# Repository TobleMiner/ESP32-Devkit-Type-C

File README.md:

ESP32 Devkit Type C
===================

This PCB is a USB Type C enabled ESP32 development board. It is pin-compatible
with the ESP32 Devkit C but sports a slightly decreased width to fit on a
standard breadboard.  
The current revision (Rev E) has been tested and confirmed to work fine.

# Features

* USB Type C
* pin-compatible with ESP32 Devkit
* fits on standard breadboard
* onboard antenna
* jumper to short USB protection diode

Furthermore this board is optimized for JLCPCB assembly, a Chinese SMT PCB
assembly service. All components on this board, except the USB Type C connector,
the push buttons and the pin headers can be assembled by them for around ~$8
including PCB manufacturing and components.

# Assembly

There is an
[interactive HTML BOM](https://tobleminer.github.io/ESP32-Devkit-Type-C/ibom.html)
to help you assemble the board.

Assuming you are using JLCPCB SMT assembly you will need to populate just the
following parts by hand:

| Reference  | Description            | LCSC                                                                                                                  |
|------------|------------------------|-----------------------------------------------------------------------------------------------------------------------|
| J1         | USB Type C connector   | [C167321](https://lcsc.com/product-detail/USB-Connectors_Jing-Extension-of-the-Electronic-Co-C167321_C167321.html)    |
| SW1, SW2   | RESET/BOOT push button | [C115357](https://lcsc.com/product-detail/Tactile-Switches_ALPS_SKRKAEE020_3-4-2-1-57N_C115357.html)    |
| J2, J3     | Pin headers            | [C2337](https://lcsc.com/product-detail/Pin-Header-Female-Header_BOOMELE-Boom-Precision-Elec-2-54mm-1x40P_C2337.html) |

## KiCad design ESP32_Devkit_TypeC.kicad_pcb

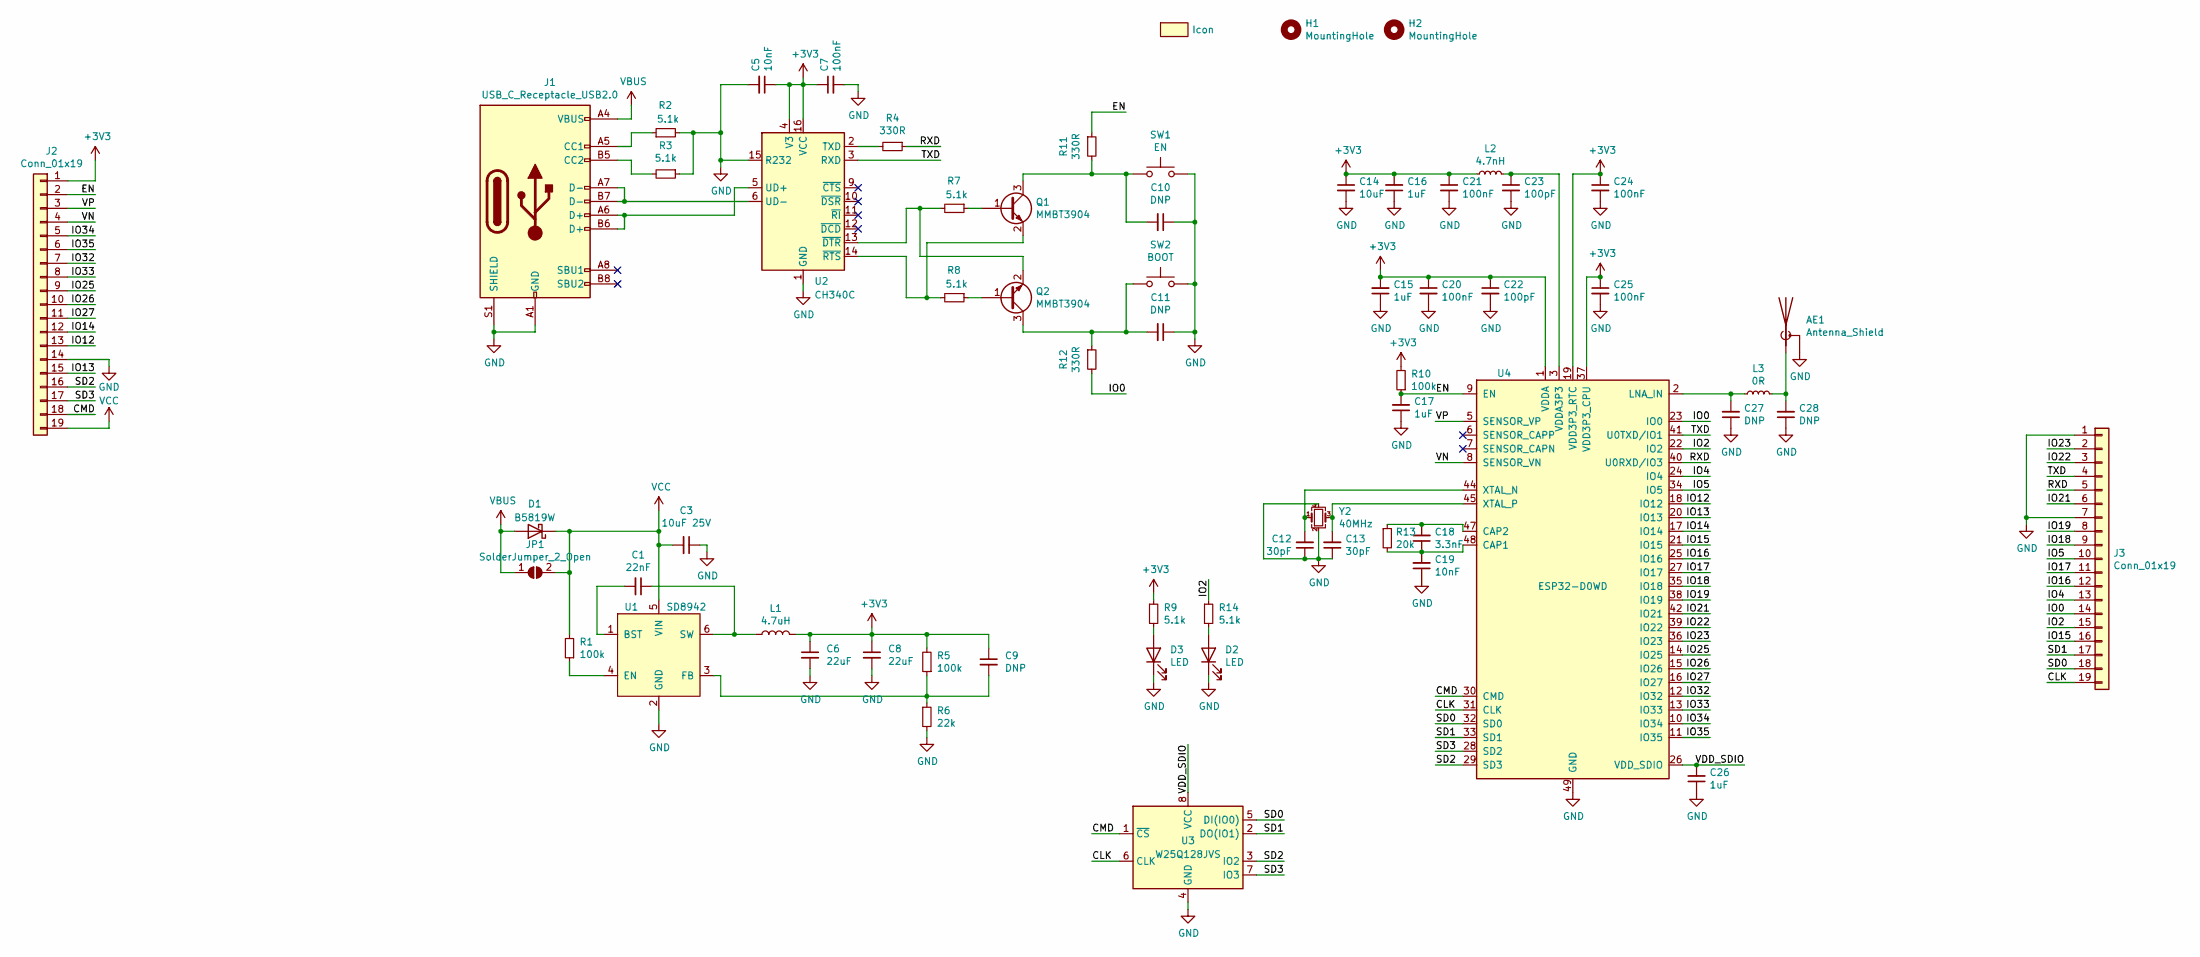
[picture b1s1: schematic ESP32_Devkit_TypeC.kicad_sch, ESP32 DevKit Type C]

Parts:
AE1: Antenna_Shield; Antenna_IFA_2.4GHz_meandered_mirrored
C1: 22nF; C_0402_1005Metric; LCSC C1532
C3: 10uF 25V; C_0805_2012Metric; LCSC C15850
C5, C19: 10nF; C_0402_1005Metric; LCSC C15195
C6, C8: 22uF; C_0603_1608Metric; LCSC C59461
C7, C20, C21, C24, C25: 100nF; C_0402_1005Metric; LCSC C1525
C9, C10, C11, C28: DNP; C_0402_1005Metric
C12, C13: 30pF; C_0402_1005Metric; LCSC C1570
C14: 10uF; C_0402_1005Metric; LCSC C15525
C15, C16, C17, C26: 1uF; C_0402_1005Metric; LCSC C52923
C18: 3.3nF; C_0402_1005Metric; LCSC C26404
C22, C23: 100pF; C_0402_1005Metric; LCSC C1546
C27: DNP; L3
D1: B5819W; D_SOD-123; LCSC C8598
D2, D3: LED; LED_0603_1608Metric_Castellated; LCSC C2286
H1, H2: MountingHole; ToolingHole_JLCSMT
I2: Icon; OSHW_icon_3.3x3
J1: USB_C_Receptacle_USB2.0; USB_C_Receptacle_Palconn_UTC16-G; LCSC C167321
J2, J3: Conn_01x19; PinHeader_1x19_P2.54mm_Vertical; LCSC C2894942
JP1: SolderJumper_2_Open; SolderJumper-2_P1.3mm_Open_Pad1.0x1.5mm
L1: 4.7uH; L_1210_3225Metric; LCSC C90319
L2: 4.7nH; L_0603_1608Metric; LCSC C13818
L3: 0R; L_0402_1005Metric; LCSC C17168
Q1, Q2: MMBT3904; SOT-23; LCSC C20526
R1, R5, R10: 100k; R_0402_1005Metric; LCSC C25741
R2, R3, R7, R8, R9, R14: 5.1k; R_0402_1005Metric; LCSC C25905
R4, R11, R12: 330R; R_0402_1005Metric; LCSC C25104
R6: 22k; R_0402_1005Metric; LCSC C25768
R13: 20k; R_0402_1005Metric; LCSC C25765
SW1: EN; SW_Push_SPST_NO_Alps_SKRK; LCSC C202388
SW2: BOOT; SW_Push_SPST_NO_Alps_SKRK; LCSC C202388
U1: SD8942; SOT-23-6; LCSC C250795
U2: CH340C; SOIC-16_3.9x9.9mm_P1.27mm; LCSCL C84681
U3: W25Q128JVS; SOIC-8_5.23x5.23mm_P1.27mm; LCSC C97521
U4: ESP32-D0WD; QFN-48-1EP_5x5mm_P0.35mm_EP3.7x3.7mm_ThermalVias; LCSC C967020
Y2: 40MHz; Crystal_SMD_2520-4Pin_2.5x2.0mm; LCSC C426970

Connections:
+3V3: C5.1, C6.1, C7.1, C8.1, C9.1, C14.1, C15.2, C16.2, C20.1, C21.1, C22.1, C24.1, C25.1, J2.1, L1.2, L2.1, R5.2, R9.1, R10.2, U2.4 (V3), U2.16 (VCC), U4.1 (VDDA), U4.19 (VDD3P3_RTC), U4.37 (VDD3P3_CPU), U4.43 (VDDA), U4.46 (VDDA)
/CLK: J3.19, U3.6 (CLK), U4.31 (CLK)
/CMD: J2.18, U3.1 (~CS), U4.30 (CMD)
/EN: C17.2, J2.2, R10.1, R11.1, U4.9 (EN)
/IO0: J3.14, R12.2, U4.23 (IO0)
/IO2: J3.15, R14.1, U4.22 (IO2)
/IO4: J3.13, U4.24 (IO4)
/IO5: J3.10, U4.34 (IO5)
/IO12: J2.13, U4.18 (IO12)
/IO13: J2.15, U4.20 (IO13)
/IO14: J2.12, U4.17 (IO14)
/IO15: J3.16, U4.21 (IO15)
/IO16: J3.12, U4.25 (IO16)
/IO17: J3.11, U4.27 (IO17)
/IO18: J3.9, U4.35 (IO18)
/IO19: J3.8, U4.38 (IO19)
/IO21: J3.6, U4.42 (IO21)
/IO22: J3.3, U4.39 (IO22)
/IO23: J3.2, U4.36 (IO23)
/IO25: J2.9, U4.14 (IO25)
/IO26: J2.10, U4.15 (IO26)
/IO27: J2.11, U4.16 (IO27)
/IO32: J2.7, U4.12 (IO32)
/IO33: J2.8, U4.13 (IO33)
/IO34: J2.5, U4.10 (IO34)
/IO35: J2.6, U4.11 (IO35)
/RXD: J3.5, R4.1, U4.40 (U0RXD/IO3)
/SD0: J3.18, U3.5 (DI(IO0)), U4.32 (SD0)
/SD1: J3.17, U3.2 (DO(IO1)), U4.33 (SD1)
/SD2: J2.16, U3.3 (IO2), U4.29 (SD3)
/SD3: J2.17, U3.7 (IO3), U4.28 (SD2)
/TXD: J3.4, U2.3 (RXD), U4.41 (U0TXD/IO1)
/VDD_SDIO: C26.2, U3.8 (VCC), U4.26 (VDD_SDIO)
/VN: J2.4, U4.8 (SENSOR_VN)
/VP: J2.3, U4.5 (SENSOR_VP)
GND: AE1.2 (Shield), C3.1, C5.2, C6.2, C7.2, C8.2, C10.1, C11.1, C12.1, C13.1, C14.2, C15.1, C16.1, C17.1, C19.1, C20.2, C21.2, C22.2, C23.2, C24.2, C25.2, C26.1, C27.1, C28.1, D2.1 (K), D3.1 (K), J1.A1 (GND), J1.A12 (GND), J1.B1 (GND), J1.B12 (GND), J1.S1 (SHIELD), J2.14, J3.1, J3.7, R2.2, R3.1, R6.2, SW1.2, SW2.2, U1.2 (GND), U2.1 (GND), U2.15 (R232), U3.4 (GND), U4.49 (GND), Y2.2, Y2.4
unnamed: AE1.1 (A), C28.2, L3.2
unnamed: C1.1, L1.1, U1.6 (SW)
unnamed: C1.2, U1.1 (BST)
unnamed: C9.2, R5.1, R6.1, U1.3 (FB)
unnamed: C10.2, Q1.3 (C), R11.2, SW1.1
unnamed: C11.2, Q2.3 (C), R12.1, SW2.1
unnamed: C12.2, U4.44 (XTAL_N), Y2.1
unnamed: C13.2, U4.45 (XTAL_P), Y2.3
unnamed: C18.1, C19.2, R13.2, U4.48 (CAP1)
unnamed: C18.2, R13.1, U4.47 (CAP2)
unnamed: C23.1, L2.2, U4.3 (VDDA3P3), U4.4 (VDDA3P3)
unnamed: C27.2, L3.1, U4.2 (LNA_IN)
unnamed: D2.2 (A), R14.2
unnamed: D3.2 (A), R9.2
unnamed: J1.A5 (CC1), R2.1
unnamed: J1.A6 (D+), J1.B6 (D+), U2.5 (UD+)
unnamed: J1.A7 (D-), J1.B7 (D-), U2.6 (UD-)
unnamed: J1.B5 (CC2), R3.2
unnamed: Q1.1 (B), R7.1
unnamed: Q1.2 (E), R8.2, U2.14 (~RTS)
unnamed: Q2.1 (B), R8.1
unnamed: Q2.2 (E), R7.2, U2.13 (~DTR)
unnamed: R1.1, U1.4 (EN)
unnamed: R4.2, U2.2 (TXD)
VBUS: D1.2 (A), J1.A4 (VBUS), J1.A9 (VBUS), J1.B4 (VBUS), J1.B9 (VBUS), JP1.1 (A)
VCC: C3.2, D1.1 (K), J2.19, JP1.2 (B), R1.2, U1.5 (VIN)

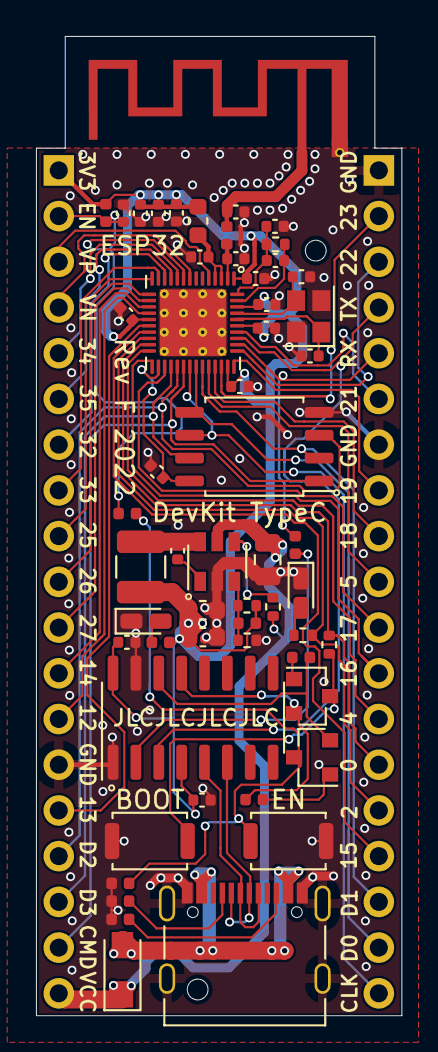
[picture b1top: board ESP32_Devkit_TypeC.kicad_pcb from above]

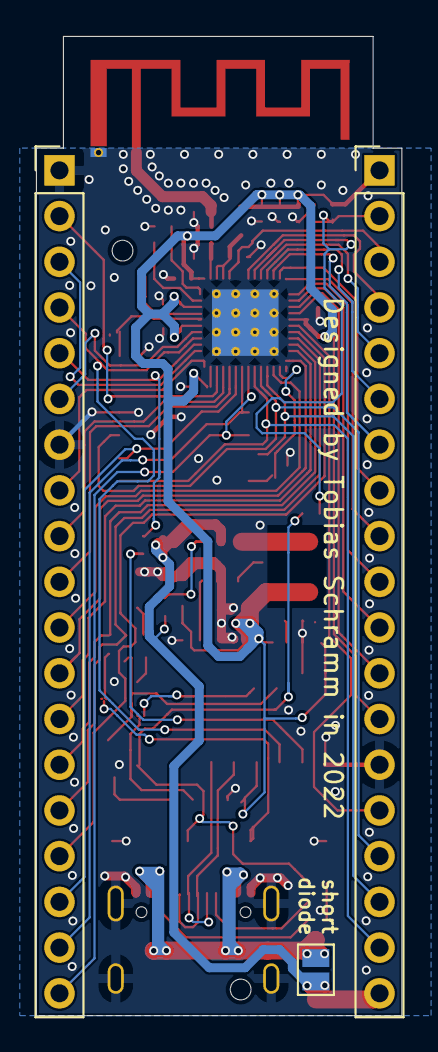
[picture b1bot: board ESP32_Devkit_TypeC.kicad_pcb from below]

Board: 2 copper layers, 20.3 x 54.4 mm, 61 parts (3 on the bottom side), 62 nets.

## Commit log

2020-05-07 Increase strength of step down enable pullup
2020-05-07 Hide all silkscreen references
2020-05-07 Add silkscreen markings
2020-05-07 Add tooling holes
2020-05-07 Reduce paste size by two percent
2020-05-08 Add more vias to VBUS
2020-05-08 Add screenshot of board
2020-05-08 Add README
2020-05-08 Ignore bak files
2020-05-08 Move features up
2020-05-08 Add OSHW logo
2020-05-08 Add 3rdparty lib folder
2020-05-08 Add fabrication files
2020-05-08 Add interactive BOM
2020-05-08 Add assembly information
2020-05-19 Add ESP32 Pico D4 package
    The ESP32 Pico D4 is not a QFN part. It is a LGA part featuring the same
    pad locations as a QFN-48 7x7 0.5mm pitch part.
2020-05-19 Use ESP32 Pico D4 footprint
2020-05-20 Rev B
    Changes from Rev A:
    - Fix ESP32 Pico D4 footprint, now LGA
    - Add couple capacitor from EN to IO0
    - Add protection resistors to EN and IO0
    - Move VBUS diode for easier USB Type C jack assembly
    - Small routing optimizations
2020-05-20 Update documentation for Rev B
2020-05-21 Update JLC gerbers to Rev B
2020-05-31 Fix step down GND routing
2020-05-31 Rev C
    Changes from Rev B:
    * Add more bypassing to ESP32 Pico D4
    * Reduce ground loop area of step-down significantly
    * Fix ugly routing of USB D+
2020-08-03 Update README.md
    Changed the right component for the RESET/BOOT push button
2020-09-29 Remove fab directory
2020-09-29 Mark printed antennas as virtual components
2020-09-29 Rev D
    Most importantly this revision improves reset/bootloader behaviour
    by increasing the RC time constant of the reset RC network considerably.
    (~50ms vs 1ms). This makes programming more reliable on machines with
    high DTR/RTS setting delays or when working with USB over IP solutions.
    Full list of changes:
    * Improve reset/flash behaviour
2020-09-29 Add RevD breadboard screenshot
2020-10-01 Rev E better bypassing
    This revision improves upon the bypassing of the ESP32 Pico D4.
    The previous bypassing was not satisfactory to me and I fear it
    might cause issues under high load conditions.
    Bypassing is improved by adding an additional 10uF capacitor to
    each power pin.
    Additionally a third 22uF capacitor has been added to icrease bulk
2020-10-02 Update screenshot to Rev E
2020-10-23 Remove disclaimer about untested design
    I've received Rev E and tested it.
2021-01-16 Add schematic pdf
2021-12-22 Start revision F layout
    The previous five revisions are not satisfactory. They have a number of
    issues:
    - Poor RF performance due to improper antenna placement and matching
    - GPIO16 and GPIO17 are unusable, inherent problem with Pico D4
    - Instability. Might be related to excessive power consumption due to
    improper antenna matching
2021-12-22 Layout primary step-down converter
2022-08-06 Layout WiP
    ESP32 should be rotated by 90°, save current layouting progress
2022-10-02 Ignore local mess of artifacts
2022-10-02 Layout revision F
2022-10-02 Add pin header partnumber
2022-10-02 Allow copper pour to flow onto antenna ground
2022-10-02 Ignore more artifacts
2022-10-02 Better RF grounding around antenna connection
2022-10-02 Setup silkscreen
2022-10-02 Remove stray pin1 dot
